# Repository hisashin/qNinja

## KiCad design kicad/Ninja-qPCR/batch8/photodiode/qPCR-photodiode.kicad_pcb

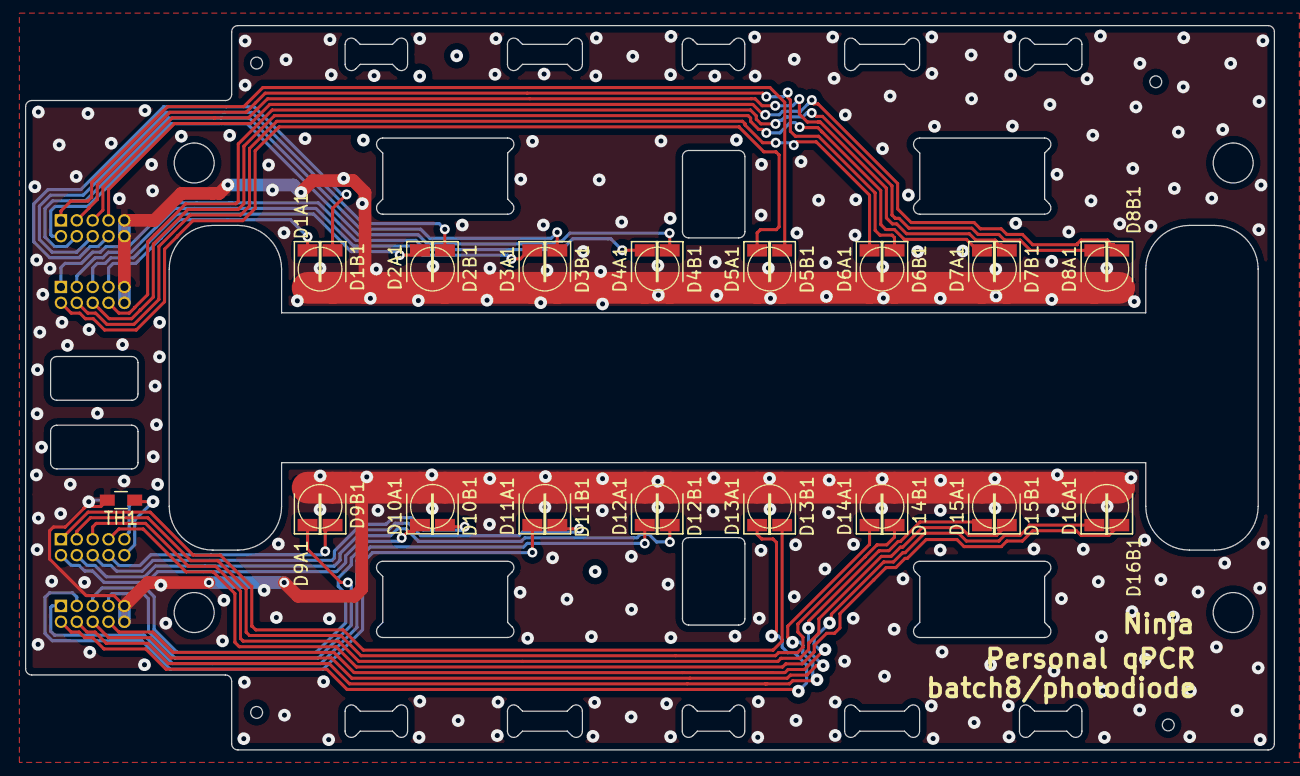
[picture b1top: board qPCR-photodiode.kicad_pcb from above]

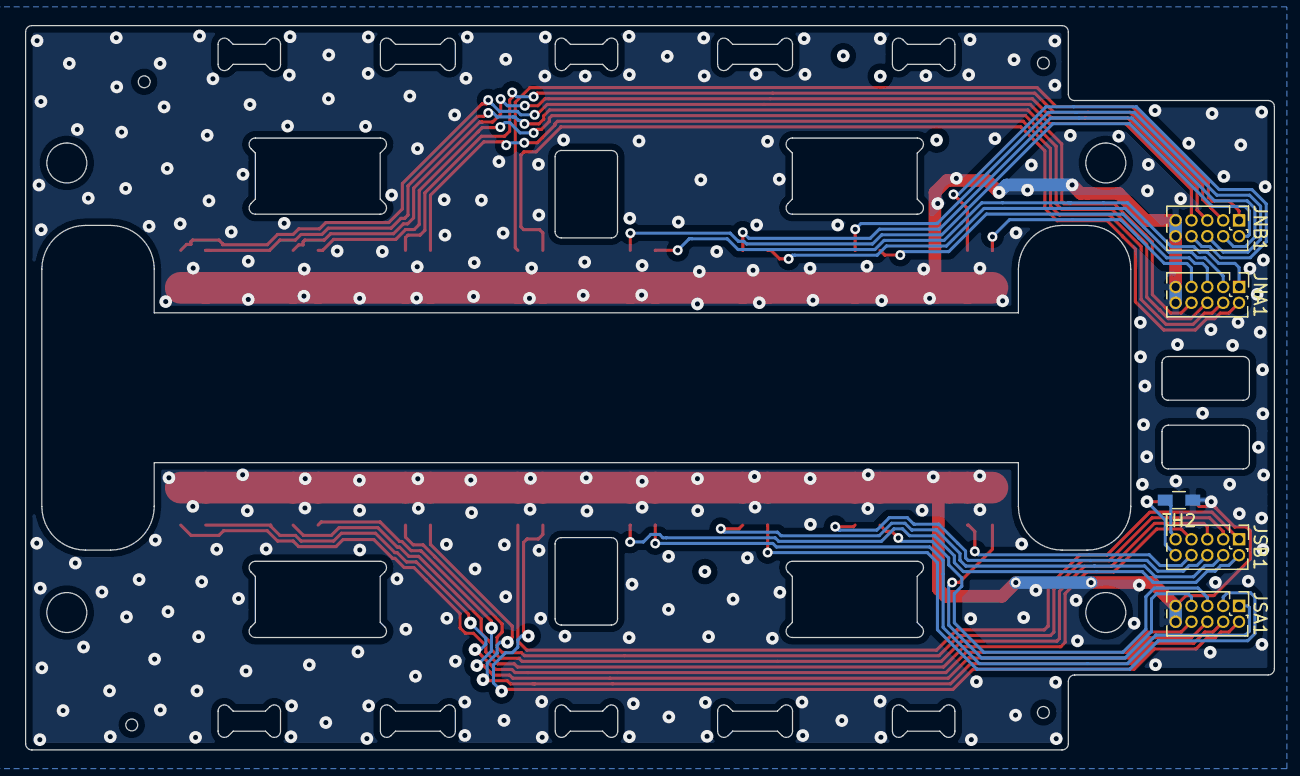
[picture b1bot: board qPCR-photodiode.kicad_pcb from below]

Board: 2 copper layers, 100.0 x 58.0 mm, 38 parts (5 on the bottom side), 35 nets.

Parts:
D1A1, D1B1, D2A1, D2B1, D3A1, D3B1, D4A1, D4B1, D5A1, D5B1, D6A1, D6B1, D7A1, D7B1, D8A1, D8B1, D9A1, D9B1, D10A1, D10B1, D11A1, D11B1, D12A1, D12B1, D13A1, D13B1, D14A1, D14B1, D15A1, D15B1, D16A1, D16B1: D_Photo; D_1206
JNA1: Conn_01x10_Male; Pin_Header_Straight_2x05_Pitch1.27mm
JNB1: Conn_01x10_Male; Pin_Header_Straight_2x05_Pitch1.27mm
JSA1: Conn_01x10_Male; Pin_Header_Straight_2x05_Pitch1.27mm
JSB1: Conn_01x10_Male; Pin_Header_Straight_2x05_Pitch1.27mm
TH1, TH2: Thermistor; R_0603_HandSoldering

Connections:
/N_PD_OUT1: D1A1.1, JNA1.7
/N_PD_OUT2: D1B1.1, JNB1.8
/N_PD_OUT3: D2A1.1, JNA1.5
/N_PD_OUT4: D2B1.1, JNB1.6
/N_PD_OUT5: D3A1.1, JNA1.3
/N_PD_OUT6: D3B1.1, JNB1.4
/N_PD_OUT7: D4A1.1, JNA1.1
/N_PD_OUT8: D4B1.1, JNB1.2
/N_PD_OUT9: D5A1.1, JNA1.2
/N_PD_OUT10: D5B1.1, JNB1.1
/N_PD_OUT11: D6A1.1, JNA1.4
/N_PD_OUT12: D6B1.1, JNB1.3
/N_PD_OUT13: D7A1.1, JNA1.6
/N_PD_OUT14: D7B1.1, JNB1.5
/N_PD_OUT15: D8A1.1, JNA1.8
/N_PD_OUT16: D8B1.1, JNB1.7
/S_PD_OUT1: D9A1.1, JSA1.7
/S_PD_OUT2: D9B1.1, JSB1.8
/S_PD_OUT3: D10A1.1, JSA1.5
/S_PD_OUT4: D10B1.1, JSB1.6
/S_PD_OUT5: D11A1.1, JSA1.3
/S_PD_OUT6: D11B1.1, JSB1.4
/S_PD_OUT7: D12A1.1, JSA1.1
/S_PD_OUT8: D12B1.1, JSB1.2
/S_PD_OUT9: D13A1.1, JSA1.2
/S_PD_OUT10: D13B1.1, JSB1.1
/S_PD_OUT11: D14A1.1, JSA1.4
/S_PD_OUT12: D14B1.1, JSB1.3
/S_PD_OUT13: D15A1.1, JSA1.6
/S_PD_OUT14: D15B1.1, JSB1.5
/S_PD_OUT15: D16A1.1, JSA1.8
/S_PD_OUT16: D16B1.1, JSB1.7
GNDA: D1A1.2, D1B1.2, D2A1.2, D2B1.2, D3A1.2, D3B1.2, D4A1.2, D4B1.2, D5A1.2, D5B1.2, D6A1.2, D6B1.2, D7A1.2, D7B1.2, D8A1.2, D8B1.2, D9A1.2, D9B1.2, D10A1.2, D10B1.2, D11A1.2, D11B1.2, D12A1.2, D12B1.2, D13A1.2, D13B1.2, D14A1.2, D14B1.2, D15A1.2, D15B1.2, D16A1.2, D16B1.2, JNA1.9, JNA1.10, JNB1.9, JNB1.10, JSA1.9, JSA1.10, TH1.2, TH2.2
unnamed: JSB1.9, TH2.1
unnamed: JSB1.10, TH1.1

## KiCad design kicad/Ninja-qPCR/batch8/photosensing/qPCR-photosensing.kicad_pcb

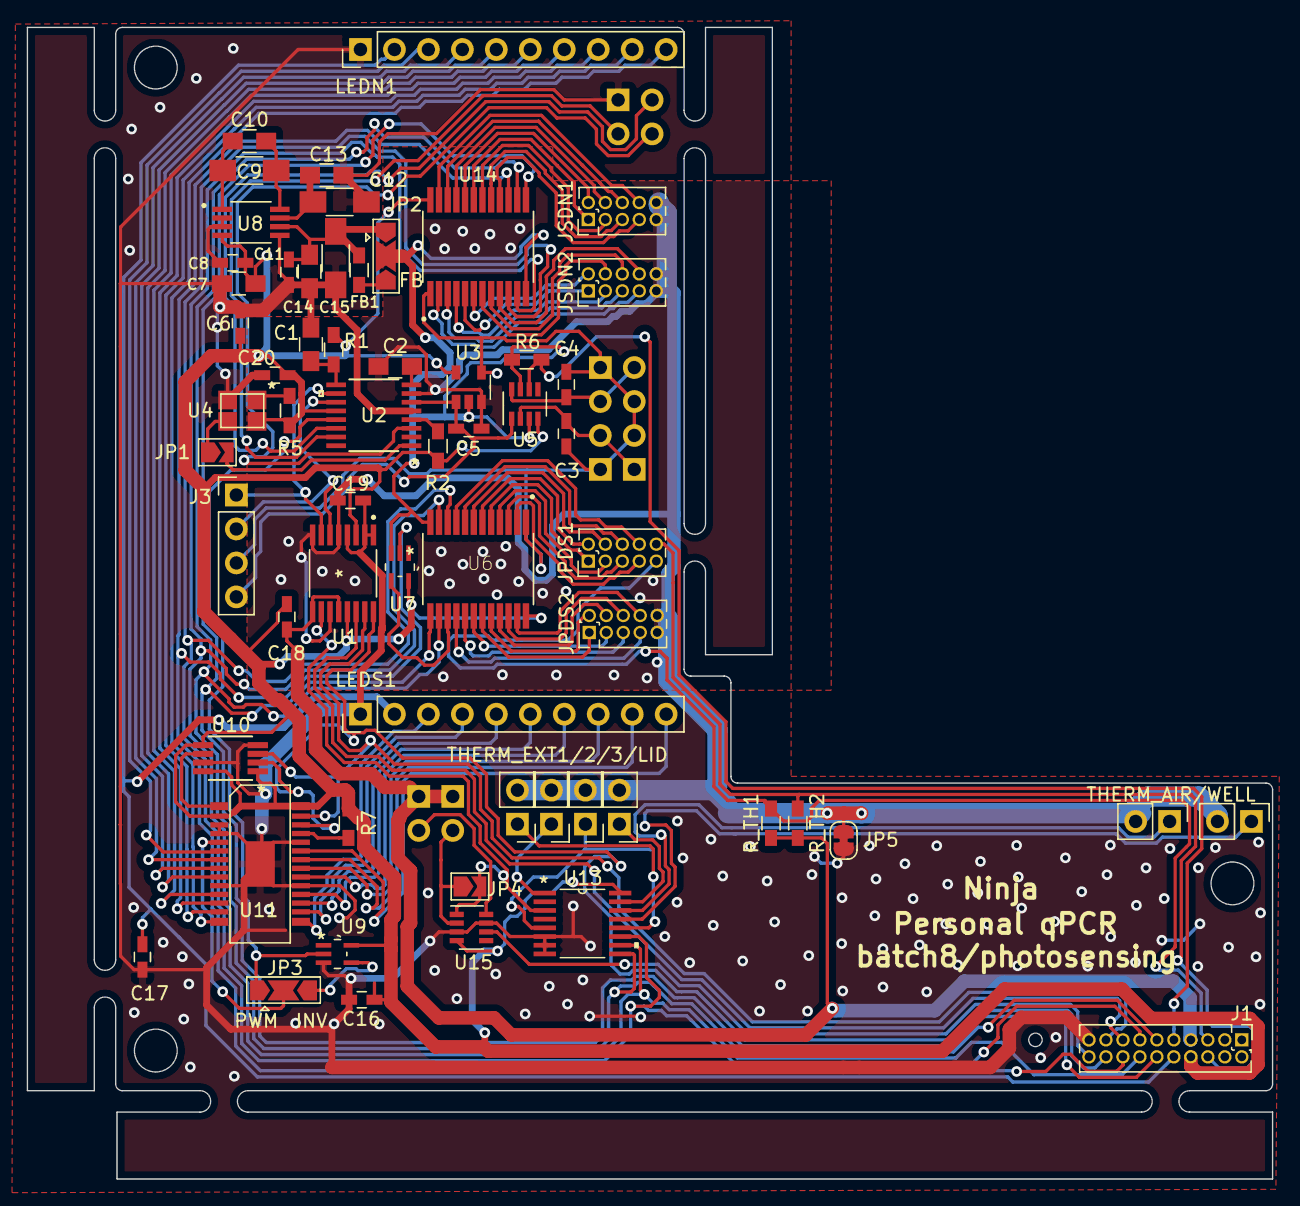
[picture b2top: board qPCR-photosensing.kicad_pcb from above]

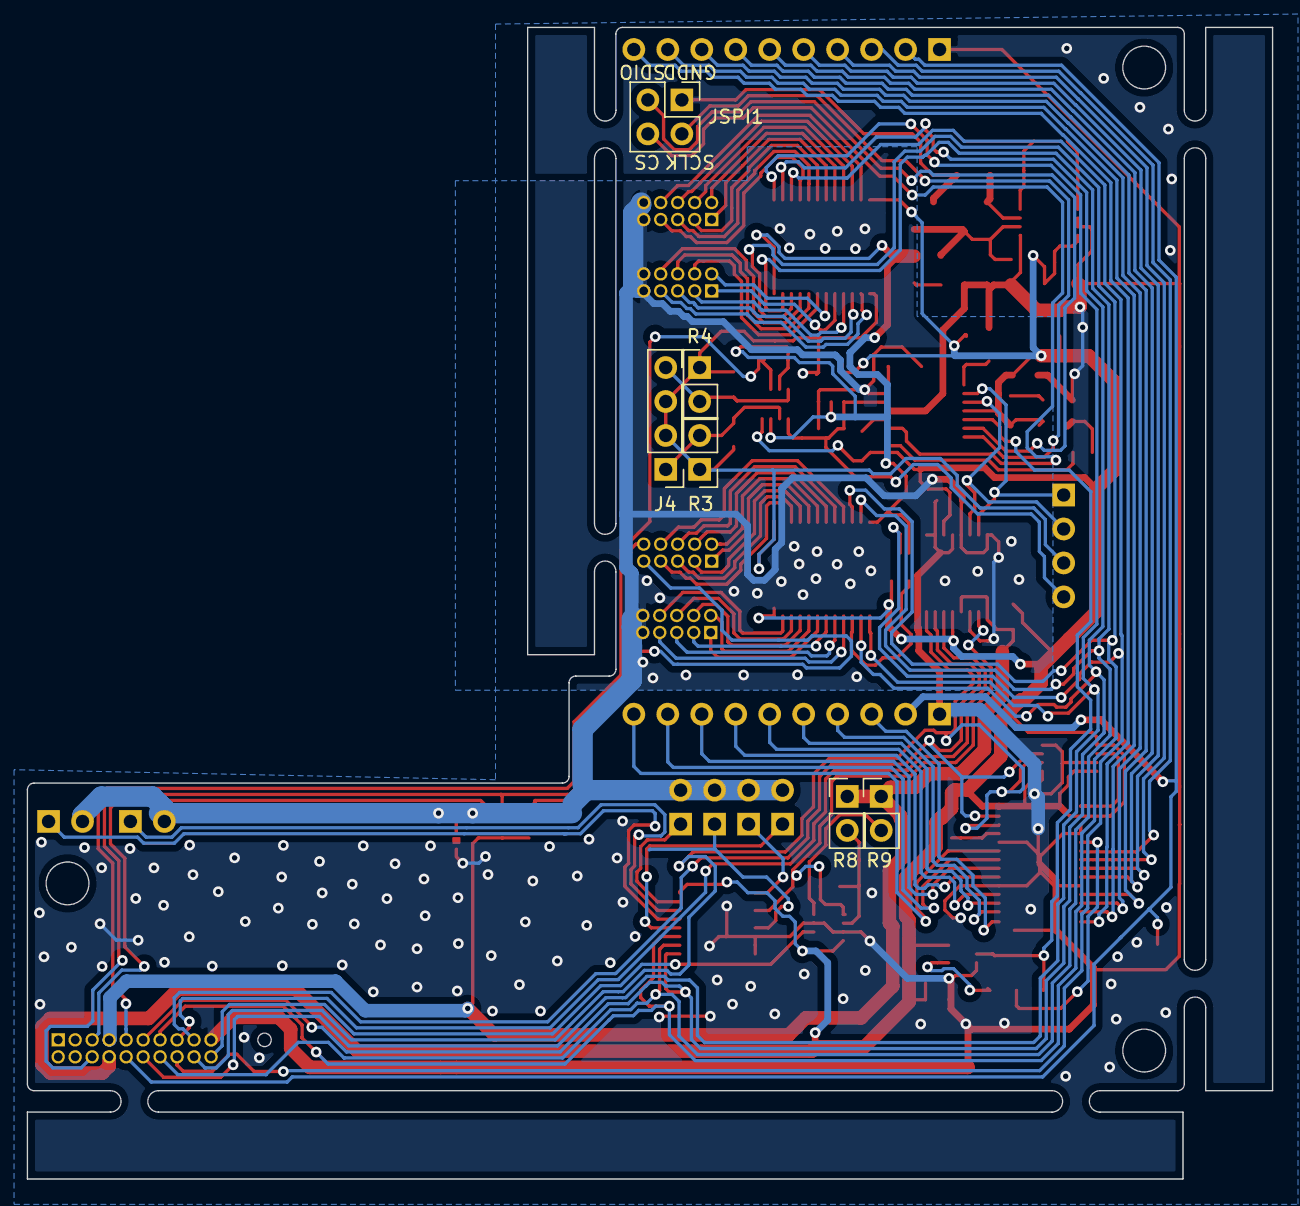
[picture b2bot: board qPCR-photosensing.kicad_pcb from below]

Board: 2 copper layers, 93.1 x 86.1 mm, 67 parts (6 on the bottom side), 101 nets.

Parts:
C1, C2, C7, C10, C13: 4.7uF; C_0805_HandSoldering
C3, C4: 22pF; C_0603_HandSoldering
C5, C6, C8, C11, C16, C17, C18, C19, C20: 0.1uF; C_0603_HandSoldering
C9, C12, C15: DNP; C_1206_HandSoldering
C14: 22uF; C_0805_HandSoldering
FB1: 120@100MHz; R_0603_HandSoldering
J1: Conn_01x20_Male; Pin_Header_Straight_2x10_Pitch1.27mm
J3, J4: Conn_01x04_Male; Pin_Header_Straight_1x04_Pitch2.54mm
JP1: Jumper; SolderJumper-2_P1.3mm_Open_TrianglePad1.0x1.5mm
JP2, JP3: Jumper_3_Open; SolderJumper-3_P2.0mm_Open_TrianglePad1.0x1.5mm
JP4: Jumper_2_Open; SolderJumper-2_P1.3mm_Open_TrianglePad1.0x1.5mm
JP5: SolderJumper_2_Bridged; SolderJumper-2_P1.3mm_Bridged_RoundedPad1.0x1.5mm
JPDS1, JPDS2: Conn_01x10_Male; Pin_Header_Straight_2x05_Pitch1.27mm
JSDN1, JSDN2: Conn_01x10_Male; Pin_Header_Straight_2x05_Pitch1.27mm
JSPI1: Conn_01x04_Male; Pin_Header_Straight_2x02_Pitch2.54mm
LEDN1: Conn_01x10_Male; Pin_Header_Straight_1x10_Pitch2.54mm
LEDS1: Conn_01x10_Male; Pin_Header_Straight_1x10_Pitch2.54mm
R1, R2, R5, R6: 10K; R_0603_HandSoldering
R3, R4: R; Pin_Header_Straight_1x02_Pitch2.54mm
R7: 47k; R_0603_HandSoldering
R8, R9: ?k; Pin_Header_Straight_1x02_Pitch2.54mm
R_TH1, R_TH2: 10K; R_0603_HandSoldering
TAIR1: Conn_01x02_Male; Pin_Header_Straight_1x02_Pitch2.54mm
TEXT1, TEXT2, TEXT3: Conn_01x02_Male; Pin_Header_Straight_1x02_Pitch2.54mm
TLID1: Conn_01x02_Male; Pin_Header_Straight_1x02_Pitch2.54mm
TWELL1: Conn_01x02_Male; Pin_Header_Straight_1x02_Pitch2.54mm
U1: ADS122C04IPWR
U2: ADA2200ARUZ
U3: LMP7717MF_NOPB; SOT-23-5
U4: COM1305-0.032768-EXT-T-TR
U5, U15: TS12A12511DCNR; SOT-23-8
U6, U14: CD74HC4067M96; SOP65P780X200-24N
U7, U9: SN74LVC1GU04DCKR
U8: LM7705MMX_NOPB; LM7705MMX-NOPB
U10: MCP4551T-503E/MS; MCP4551T-502E&slash_MS
U11: PCA9955B
U13: SN74LV4051APWR

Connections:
3V3A: C18.1, J1.7, R8.1, R9.1, R_TH1.2, R_TH2.2, U1.9, U1.12
3V3D: C6.1, C7.2, C8.2, C16.1, C18.2, C20.1, J1.8, R1.2, R2.2, R5.2, R7.2, U1.3, U1.13, U2.12, U3.5, U4.4, U5.4, U6.24, U7.5, U8.4, U9.5, U10.1, U10.5, U10.8, U11.2, U11.28, U13.16, U14.24, U15.4
-1V: JP2.2, R6.2, U3.2, U5.3, U5.7, U6.12, U7.3, U14.12
/AMP_OUT: C5.2, J3.4, U2.6, U3.1, U5.1
/GAIN_LARGE: C3.1, J4.1, R3.2, U5.2
/GAIN_SMALL: C4.1, J4.4, R4.2, U5.8
/LED/LED_BLANK: JP3.2, U11.5
/LED/LED_IREF: U10.6, U11.1
/PHOTO_OUT_N: J3.1, U1.7, U2.10
/PHOTO_OUT_P: J3.2, U1.6, U2.11
/Sheet60AF0517/MUX_SELECT_INV: U6.15, U7.4
/Sheet60AF0517/S_PD_OUT1: JPDS2.8, U6.23
/Sheet60AF0517/S_PD_OUT2: JPDS1.7, U6.2
/Sheet60AF0517/S_PD_OUT3: JPDS2.6, U6.22
/Sheet60AF0517/S_PD_OUT4: JPDS1.5, U6.3
/Sheet60AF0517/S_PD_OUT5: JPDS2.4, U6.21
/Sheet60AF0517/S_PD_OUT6: JPDS1.3, U6.4
/Sheet60AF0517/S_PD_OUT7: JPDS2.2, U6.20
/Sheet60AF0517/S_PD_OUT8: JPDS1.1, U6.5
/Sheet60AF0517/S_PD_OUT9: JPDS2.1, U6.19
/Sheet60AF0517/S_PD_OUT10: JPDS1.2, U6.6
/Sheet60AF0517/S_PD_OUT11: JPDS2.3, U6.18
/Sheet60AF0517/S_PD_OUT12: JPDS1.4, U6.7
/Sheet60AF0517/S_PD_OUT13: JPDS2.5, U6.17
/Sheet60AF0517/S_PD_OUT14: JPDS1.6, U6.8
/Sheet60AF0517/S_PD_OUT15: JPDS2.7, U6.16
/Sheet60AF0517/S_PD_OUT16: JPDS1.8, U6.9
/Sheet60C04E5B/N_PD_OUT1: JSDN2.8, U14.9
/Sheet60C04E5B/N_PD_OUT2: JSDN1.7, U14.16
/Sheet60C04E5B/N_PD_OUT3: JSDN2.6, U14.8
/Sheet60C04E5B/N_PD_OUT4: JSDN1.5, U14.17
/Sheet60C04E5B/N_PD_OUT5: JSDN2.4, U14.7
/Sheet60C04E5B/N_PD_OUT6: JSDN1.3, U14.18
/Sheet60C04E5B/N_PD_OUT7: JSDN2.2, U14.6
/Sheet60C04E5B/N_PD_OUT8: JSDN1.1, U14.19
/Sheet60C04E5B/N_PD_OUT9: JSDN2.1, U14.5
/Sheet60C04E5B/N_PD_OUT10: JSDN1.2, U14.20
/Sheet60C04E5B/N_PD_OUT11: JSDN2.3, U14.4
/Sheet60C04E5B/N_PD_OUT12: JSDN1.4, U14.21
/Sheet60C04E5B/N_PD_OUT13: JSDN2.5, U14.3
/Sheet60C04E5B/N_PD_OUT14: JSDN1.6, U14.22
/Sheet60C04E5B/N_PD_OUT15: JSDN2.7, U14.2
/Sheet60C04E5B/N_PD_OUT16: JSDN1.8, U14.23
ADC_DRDY: J1.15, U1.14
AMP_GAIN_SW: J1.9, R6.1, U5.6
CLKIN: JP1.2, U2.1
DEMOD_SPI_CS: JSPI1.4, U2.3
DEMOD_SPI_SCLK: JSPI1.2, U2.15
DEMOD_SPI_SDIO: JSPI1.3, U2.14
GNDA: C2.2, C5.1, C19.1, JP5.2, JPDS2.9, JPDS2.10, JSDN1.9, JSDN1.10, JSDN2.9, JSDN2.10, TAIR1.2, TEXT1.2, TEXT2.2, TEXT3.2, TLID1.2, TWELL1.2, U1.5, U1.8, U1.11, U2.7, U3.3
GNDD: C1.2, C6.2, C7.1, C8.1, C11.1, C12.1, C13.1, C14.1, C15.1, C16.2, C17.2, C19.2, C20.2, J1.19, JP5.1, JSPI1.1, LEDN1.1, LEDS1.1, U1.1, U1.2, U1.4, U2.5, U4.2, U8.2, U8.3, U8.5, U9.3, U10.4, U10.7, U11.3, U11.4, U11.10, U11.19, U11.24, U11.29, U13.6, U13.7, U13.8, U15.3, U15.7
I2C_SCL: J1.18, U1.16, U10.2, U11.26
I2C_SDA: J1.17, U1.15, U10.3, U11.27
MUX_S0: J1.13, U6.10, U13.11, U14.10
MUX_S1: J1.14, U6.11, U13.10, U14.11
MUX_S2: J1.11, U6.14, U13.9, U14.14
MUX_S3: J1.12, U6.13, U14.13
MUX_SELECT: J1.16, U7.2, U14.15
N_LED_OUT1: LEDN1.3, U11.6
N_LED_OUT2: LEDN1.4, U11.7
N_LED_OUT3: LEDN1.5, U11.8
N_LED_OUT4: LEDN1.6, U11.9
N_LED_OUT5: LEDN1.7, U11.11
N_LED_OUT6: LEDN1.8, U11.12
N_LED_OUT7: LEDN1.9, U11.13
N_LED_OUT8: LEDN1.10, U11.14
unnamed: C1.1, R1.1, U2.9
unnamed: C2.1, U2.8
unnamed: C9.1, C10.1, U8.8
unnamed: C9.2, C10.2, U8.1
unnamed: C11.2, C14.2, C15.2, FB1.2, JP2.1, U8.6
unnamed: C12.2, C13.2, U8.7
unnamed: FB1.1, JP2.3
unnamed: JP1.1, U4.3
unnamed: JP3.3, U9.4
unnamed: JP4.1, R8.2, U15.2
unnamed: R2.1, U2.4
unnamed: R5.1, U4.1
unnamed: R7.1, U11.25
unnamed: R9.2, U15.8
PD_MUX_OUT: C3.2, C4.2, J3.3, J4.2, J4.3, R3.1, R4.1, U3.4, U6.1, U14.1
PD_REF_PWM: JP3.1, U2.13, U9.2
PD_TH1: J1.5, JPDS1.9, R_TH1.1
PD_TH2: J1.6, JPDS1.10, R_TH2.1
S_LED_OUT1: LEDS1.3, U11.15
S_LED_OUT2: LEDS1.4, U11.16
S_LED_OUT3: LEDS1.5, U11.17
S_LED_OUT4: LEDS1.6, U11.18
S_LED_OUT5: LEDS1.7, U11.20
S_LED_OUT6: LEDS1.8, U11.21
S_LED_OUT7: LEDS1.9, U11.22
S_LED_OUT8: LEDS1.10, U11.23
THERM_AIR: TAIR1.1, U13.14
THERM_EXT1: TEXT1.1, U13.12
THERM_EXT2: TEXT2.1, U13.1
THERM_EXT3: TEXT3.1, U13.5
THERM_LID: TLID1.1, U13.15
THERM_MUX_OUT: JP4.2, U1.10, U13.3, U15.1
THERM_R_SWITCH: J1.20, U15.6
THERM_WELL: TWELL1.1, U13.13
VCC_LED: C17.1, J1.10, LEDN1.2, LEDS1.2

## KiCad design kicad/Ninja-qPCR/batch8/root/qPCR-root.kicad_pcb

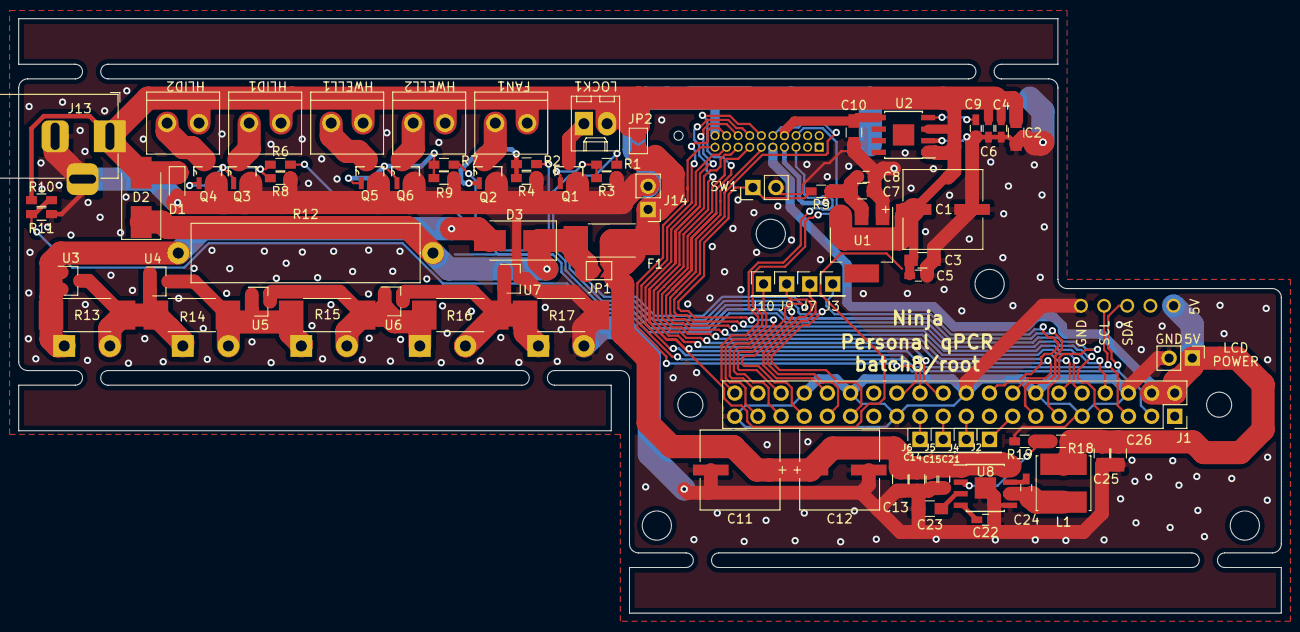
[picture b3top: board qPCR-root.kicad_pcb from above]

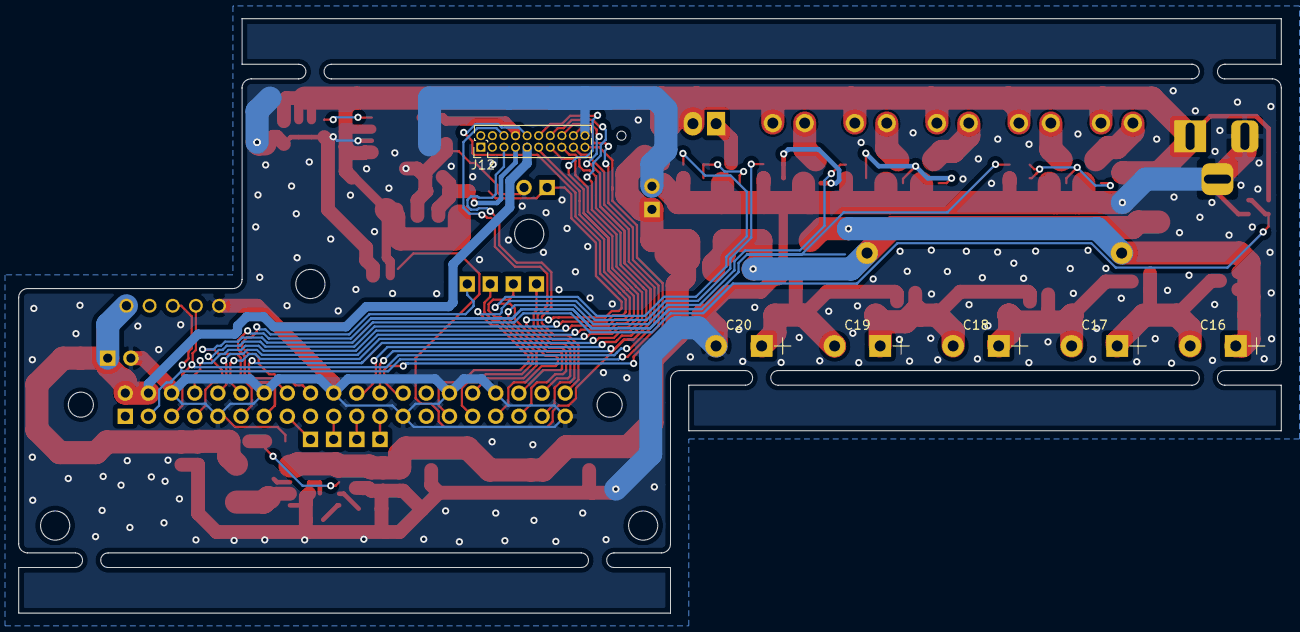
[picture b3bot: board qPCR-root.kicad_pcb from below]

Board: 2 copper layers, 138.5 x 65.2 mm, 87 parts (6 on the bottom side), 54 nets.

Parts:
C1, C11, C12: 100uF; UWX1E101MCL1GB
C2, C10, C13, C14, C23: 4.7uF; C_0805_HandSoldering
C3, C7, C25, C26: 22uF; C_0805_HandSoldering
C4, C5, C8, C15, C24: 0.1uF; C_0603_HandSoldering
C6, C21, C22: 0.01uF; C_0603_HandSoldering
C9: 100pF; C_0603_HandSoldering
C16, C17, C18, C19, C20: 10F2.7V; CP_Radial_P5.00mm
D1: D_Schottky; D_SOD-323_HandSoldering
D2, D3: D; D_SMB_Handsoldering
F1: Fuse; R_2512_HandSoldering
FAN1: Screw_Terminal_01x02; TB_SeeedOPL_320110028
HLID1, HLID2: Screw_Terminal_01x02; TB_SeeedOPL_320110028
HWELL1, HWELL2: Screw_Terminal_01x02; TB_SeeedOPL_320110028
J1: Raspberry_Pi_3A_Plus_wpi; Raspberry_Pi_3A+_3B+_4B_FaceDown_TopOnly
J2, J3, J4, J5, J6, J7, J9, J10: Conn_01x01_Male; Pin_Header_Straight_1x01_Pitch2.54mm
J12: Conn_01x20_Male; Pin_Header_Straight_2x10_Pitch1.27mm
J13: Barrel_Jack_Switch; BarrelJack_Horizontal
J14: Conn_01x02_Male; Pin_Header_Straight_1x02_Pitch2.54mm
JP1, JP2: Jumper; SolderJumper-2_P1.3mm_Open_TrianglePad1.0x1.5mm
L1: 3.3uH(ALPS GLMC / TDK SPM6530); SRN6045TA-3R3Y
LCD1: RPI_LCD_TOUCH_7INCH; RPI_LCD_TOUCH_7INCH_M2.5NONE
LCD1_POWER1: Conn_01x02_Male; Pin_Header_Straight_1x02_Pitch2.54mm
LOCK1: Conn_01x02_Male; Molex_KK-6410-02_02x2.54mm_Straight
Q1, Q2, Q3, Q4, Q5, Q6: Q_NMOS_GSD; SOT95P240X112-3N
R1, R2, R6, R7: 150; R_0603_HandSoldering
R3, R4, R5, R8, R9, R10, R19: 47k; R_0603_HandSoldering
R11: 10k; R_0603_HandSoldering
R12: 8.2Ω 3W; R_Axial_Power_L25.0mm_W6.4mm_P27.94mm
R13, R14, R15, R16, R17: 1k2W; R_2512_HandSoldering
R18: 261k; R_0603_HandSoldering
SW1: SW_Reed; Pin_Header_Straight_1x02_Pitch2.54mm
U1: CJT1117-3.3; SOT-223
U2: AP2210K-3.3TRG1; SOIC-8-1EP_3.9x4.9mm_Pitch1.27mm
U3, U4, U5, U6, U7: TL431DBZ; SOT-23
U8: BD9D320EFJ-E2; SOIC-8-1EP_3.9x4.9mm_Pitch1.27mm

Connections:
3V3A: C10.1, J12.8, U2.5
3V3D: C7.1, C8.1, J12.7, R5.1, U1.2
5V_UPS: C25.1, C26.1, J1.2, J1.4, J12.9, L1.2, LCD1.1, LCD1_POWER1.1, R18.1
12V: C1.1, C2.1, C3.1, C4.1, C5.1, C6.1, D1.1, D2.2, FAN1.1, HLID1.1, HLID2.1, HWELL1.1, HWELL2.1, J13.1, JP2.1, LOCK1.2, R10.1, U1.3, U2.1, U2.3
12V_BD_VIN: C11.1, C12.1, C13.1, C14.1, C15.1, C21.1, F1.1, J14.1, JP1.2, JP2.2, U8.1, U8.8
/FAN: J1.29, R2.2
/GPIO3: J1.15, J2.1
/GPIO5: J1.18, J3.1
/GPIO12: J1.19, J4.1
/GPIO13: J1.21, J5.1
/GPIO14: J1.23, J6.1
/GPIO22: J1.31, J7.1
/GPIO26: J1.32, J9.1
/GPIO28: J1.38, J10.1
/LID_HEATER: J1.13, R6.2
/SheetSupercap/BD_BOOT: C24.1, U8.7
/SheetSupercap/BD_FB: R18.2, R19.1, U8.2
/SheetSupercap/BD_SW: C24.2, L1.1, U8.6
/WELL_HEATER: J1.33, R7.2
ADC_DRDY: J1.24, J12.16
AMP_GAIN_SW: J1.7, J12.10
DLOCK: J1.36, R1.2
DOPEN: J1.35, R5.2, SW1.1
GND: C1.2, C2.2, C3.2, C4.2, C5.2, C6.2, C7.2, C8.2, C9.2, C10.2, C11.2, C12.2, C13.2, C14.2, C15.2, C20.2, C21.2, C22.2, C23.2, C25.2, C26.2, D1.2, J1.6, J1.9, J1.14, J1.20, J1.25, J1.30, J1.34, J1.39, J12.20, J13.2, J13.3, J14.2, LCD1.5, LCD1_POWER1.2, Q1.2, Q2.2, Q3.2, Q4.2, Q5.2, Q6.2, R3.1, R4.1, R8.1, R9.1, R11.2, R17.1, R19.2, SW1.2, U1.1, U2.2, U7.3, U8.5, U8.9
I2C_SCL: J1.5, J12.17, LCD1.4
I2C_SDA: J1.3, J12.18, LCD1.3
MUX_S0: J1.16, J12.14
MUX_S1: J1.12, J12.13
MUX_S2: J1.10, J12.12
MUX_S3: J1.8, J12.11
MUX_SELECT: J1.22, J12.15
unnamed: C9.1, U2.4
unnamed: C16.1, D3.2, R12.1, R13.2, U3.1, U3.2
unnamed: C16.2, C17.1, R13.1, R14.2, U3.3, U4.1, U4.2
unnamed: C17.2, C18.1, R14.1, R15.2, U4.3, U5.1, U5.2
unnamed: C18.2, C19.1, R15.1, R16.2, U5.3, U6.1, U6.2
unnamed: C19.2, C20.1, R16.1, R17.2, U6.3, U7.1, U7.2
unnamed: C22.1, U8.4
unnamed: C23.1, U8.3
unnamed: D2.1, D3.1, F1.2, JP1.1, R12.2
unnamed: FAN1.2, Q2.3
unnamed: HLID1.2, Q3.3
unnamed: HLID2.2, Q4.3
unnamed: HWELL1.2, Q5.3
unnamed: HWELL2.2, Q6.3
unnamed: LOCK1.1, Q1.3
unnamed: Q1.1, R1.1, R3.2
unnamed: Q2.1, R2.1, R4.2
unnamed: Q3.1, Q4.1, R6.1, R8.2
unnamed: Q5.1, Q6.1, R7.1, R9.2
PD_TH1: J1.37, J12.6
PD_TH2: J1.40, J12.5
THERM_R_SWITCH: J1.26, J12.19
VIN_SENSE: J1.11, R10.2, R11.1

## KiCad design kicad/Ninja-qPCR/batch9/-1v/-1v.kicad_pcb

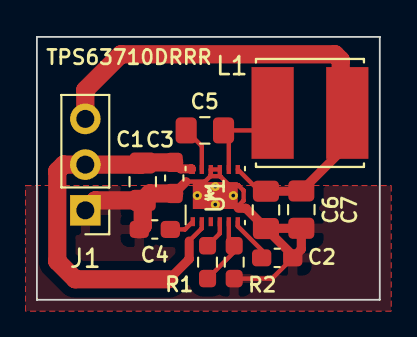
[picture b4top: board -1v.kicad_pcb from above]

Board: 2 copper layers, 19.1 x 14.6 mm, 12 parts (0 on the bottom side), 9 nets.

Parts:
C1, C6, C7: 22uF; C_0805_2012Metric_Pad1.18x1.45mm_HandSolder
C2: 1uF; C_0603_1608Metric_Pad1.08x0.95mm_HandSolder
C3: 2.2uF; C_0603_1608Metric_Pad1.08x0.95mm_HandSolder
C4: 220nF; C_0603_1608Metric_Pad1.08x0.95mm_HandSolder
C5: 10uF; C_0805_2012Metric_Pad1.18x1.45mm_HandSolder
J1: Conn_01x03_Female; Pin_Header_Straight_1x03_Pitch2.54mm
L1: 22uH; SRN6045TA-3R3Y
R1: 51.1k; R_0603_1608Metric_Pad0.98x0.95mm_HandSolder
R2: 180k; R_0603_1608Metric_Pad0.98x0.95mm_HandSolder
U1: TPS63710DRRR

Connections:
3V3: C1.1, C3.1, J1.2, U1.2, U1.12
-1V: C6.1, C7.1, J1.3, L1.2, U1.7
GND: C1.2, C2.2, C3.2, C4.2, C6.2, C7.2, J1.1, R2.2, U1.9, U1.10, U1.13
unnamed: C2.1, U1.6
unnamed: C4.1, U1.1
unnamed: C5.1, U1.11
unnamed: C5.2, L1.1, U1.8
unnamed: R1.1, U1.4
unnamed: R1.2, R2.1, U1.5

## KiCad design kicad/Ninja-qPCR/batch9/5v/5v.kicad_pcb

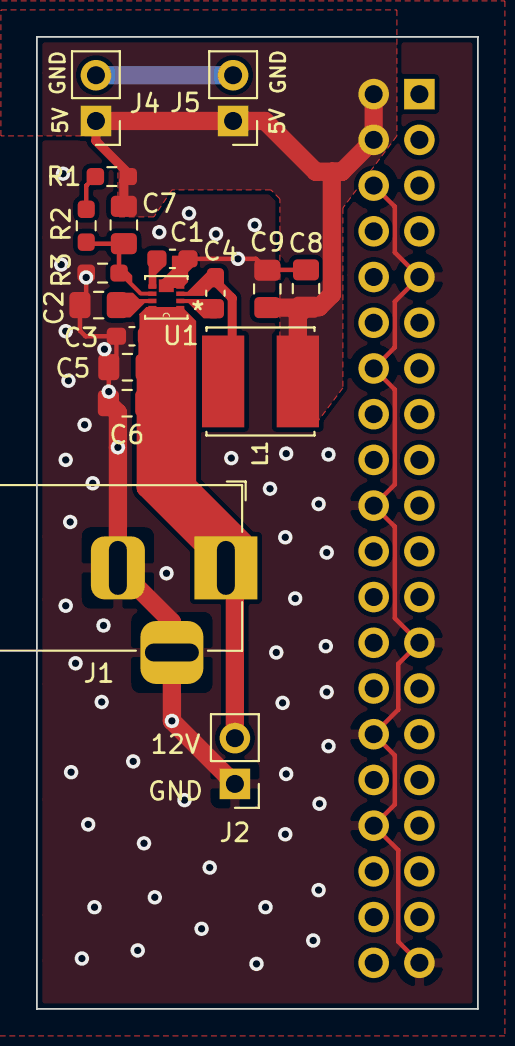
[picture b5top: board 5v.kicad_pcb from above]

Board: 2 copper layers, 24.5 x 54.0 mm, 19 parts (1 on the bottom side), 9 nets.

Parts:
C1: 330pF; C_0603_1608Metric_Pad1.08x0.95mm_HandSolder
C2: 1uF; C_0805_2012Metric_Pad1.18x1.45mm_HandSolder
C3, C4: 0.1uF; C_0603_1608Metric_Pad1.08x0.95mm_HandSolder
C5, C6: 10uF; C_0805_2012Metric_Pad1.18x1.45mm_HandSolder
C7: 22pF; C_0805_2012Metric_Pad1.18x1.45mm_HandSolder
C8, C9: 22uF; C_0805_2012Metric_Pad1.18x1.45mm_HandSolder
J1: Barrel_Jack_Switch; BarrelJack_Horizontal
J2, J4, J5: Conn_01x02_Female; Pin_Header_Straight_1x02_Pitch2.54mm
J8: Conn_02x20_Odd_Even; Pin_Header_Straight_2x20_Pitch2.54mm
L1: 3.3uF; SRN6045TA-3R3Y
R1: 1.8k; R_0603_1608Metric_Pad0.98x0.95mm_HandSolder
R2: 120k; R_0603_1608Metric_Pad0.98x0.95mm_HandSolder
R3: 22k; R_0603_1608Metric_Pad0.98x0.95mm_HandSolder
U1: UMMP008Z2020_ROM; BD9D323QWZ-E2

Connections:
5V: C7.2, C8.2, C9.2, J4.1, J5.1, J8.2, J8.4, L1.1, R1.1
12V: C3.2, C5.2, C6.2, J1.1, J2.2, U1.1, U1.8
/FB: C7.1, R2.2, R3.1, U1.6
/SS: C1.2, U1.5
GND: C1.1, C2.1, C3.1, C5.1, C6.1, C8.1, C9.1, J1.2, J1.3, J2.1, J4.2, J5.2, J8.6, J8.9, J8.14, J8.20, J8.25, J8.30, J8.34, J8.39, R3.2, U1.4, U1.9
unnamed: C2.2, U1.7
unnamed: C4.1, L1.2, U1.3
unnamed: C4.2, U1.2
unnamed: R1.2, R2.1

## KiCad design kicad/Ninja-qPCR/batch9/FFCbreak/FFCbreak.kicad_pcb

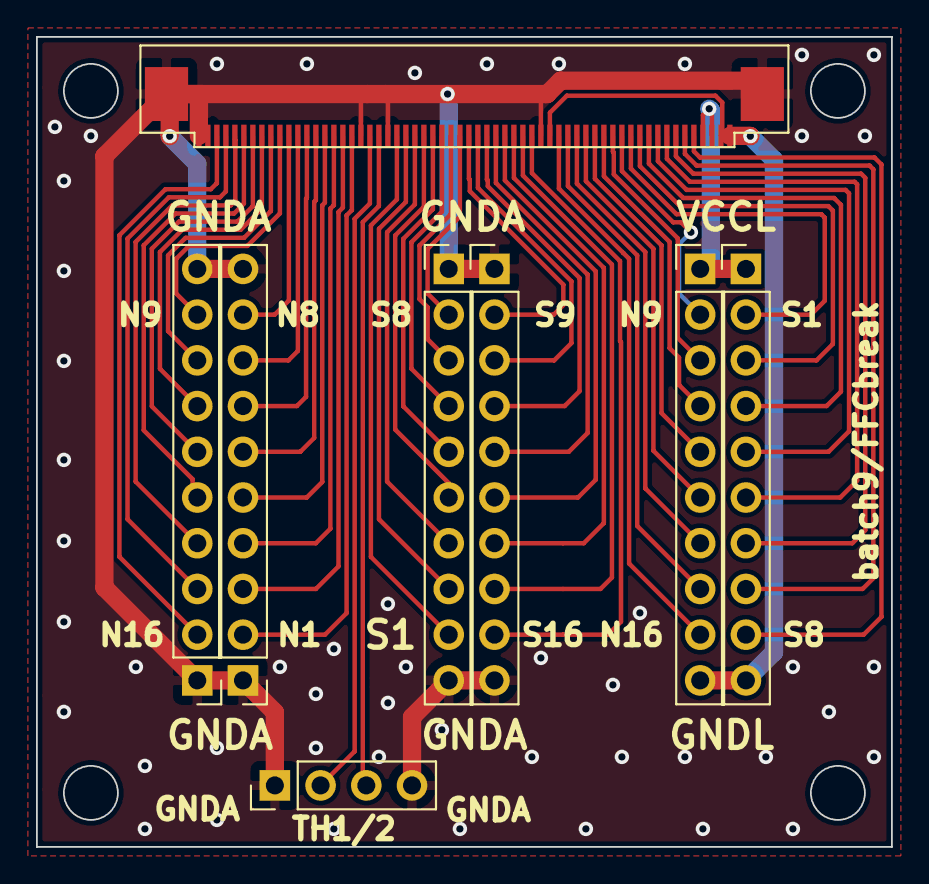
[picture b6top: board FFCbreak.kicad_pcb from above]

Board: 2 copper layers, 47.5 x 45.0 mm, 8 parts (0 on the bottom side), 53 nets.

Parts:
J1: Conn_01x60_Male; FFC_60_Ali_HUISHUNFA
J2, J3, J4, J5, J6, J7: Conn_01x10_Male; Pin_Header_Straight_1x10_Pitch2.54mm
J8: Conn_01x04_Male; Pin_Header_Straight_1x04_Pitch2.54mm

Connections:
/N_LED_OUT9: J1.13, J3.2
/N_LED_OUT10: J1.14, J3.3
/N_LED_OUT11: J1.15, J3.4
/N_LED_OUT12: J1.16, J3.5
/N_LED_OUT13: J1.17, J3.6
/N_LED_OUT14: J1.18, J3.7
/N_LED_OUT15: J1.19, J3.8
/N_LED_OUT16: J1.20, J3.9
/N_PD_OUT1: J1.43, J6.2
/N_PD_OUT2: J1.44, J6.3
/N_PD_OUT3: J1.45, J6.4
/N_PD_OUT4: J1.46, J6.5
/N_PD_OUT5: J1.47, J6.6
/N_PD_OUT6: J1.48, J6.7
/N_PD_OUT7: J1.49, J6.8
/N_PD_OUT8: J1.50, J6.9
/N_PD_OUT9: J1.51, J7.9
/N_PD_OUT10: J1.52, J7.8
/N_PD_OUT11: J1.53, J7.7
/N_PD_OUT12: J1.54, J7.6
/N_PD_OUT13: J1.55, J7.5
/N_PD_OUT14: J1.56, J7.4
/N_PD_OUT15: J1.57, J7.3
/N_PD_OUT16: J1.58, J7.2
/S_LED_OUT1: J1.12, J2.2
/S_LED_OUT2: J1.11, J2.3
/S_LED_OUT3: J1.10, J2.4
/S_LED_OUT4: J1.9, J2.5
/S_LED_OUT5: J1.8, J2.6
/S_LED_OUT6: J1.7, J2.7
/S_LED_OUT7: J1.6, J2.8
/S_LED_OUT8: J1.5, J2.9
/S_PD_OUT1: J1.38, J4.9
/S_PD_OUT2: J1.37, J4.8
/S_PD_OUT3: J1.36, J4.7
/S_PD_OUT4: J1.35, J4.6
/S_PD_OUT5: J1.34, J4.5
/S_PD_OUT6: J1.33, J4.4
/S_PD_OUT7: J1.32, J4.3
/S_PD_OUT8: J1.31, J4.2
/S_PD_OUT9: J1.30, J5.2
/S_PD_OUT10: J1.29, J5.3
/S_PD_OUT11: J1.28, J5.4
/S_PD_OUT12: J1.27, J5.5
/S_PD_OUT13: J1.26, J5.6
/S_PD_OUT14: J1.25, J5.7
/S_PD_OUT15: J1.24, J5.8
/S_PD_OUT16: J1.23, J5.9
/TH1: J1.41, J8.2
/TH2: J1.40, J8.3
GNDA: J1.22, J1.39, J1.42, J1.59, J1.60, J1.G1, J1.G2, J4.1, J4.10, J5.1, J5.10, J6.1, J6.10, J7.1, J7.10, J8.1, J8.4
GNDL: J1.1, J1.2, J1.21, J2.10, J3.10
VCCL: J1.3, J1.4, J2.1, J3.1

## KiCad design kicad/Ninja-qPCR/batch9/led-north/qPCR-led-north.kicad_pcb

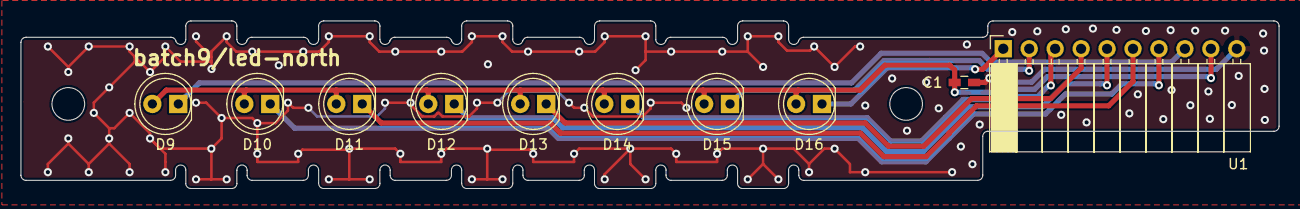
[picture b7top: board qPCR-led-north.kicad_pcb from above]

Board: 2 copper layers, 123.1 x 16.4 mm, 10 parts (0 on the bottom side), 10 nets.

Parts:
C1: C; C_0603_HandSoldering
D9, D10, D11, D12, D13, D14, D15, D16: LED; LED_D5.0mm
U1: Conn_02x05; Socket_Strip_Angled_1x10_Pitch2.54mm

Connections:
GND: C1.2, U1.10
OUT9: D9.1, U1.8
OUT10: D10.1, U1.7
OUT11: D11.1, U1.6
OUT12: D12.1, U1.5
OUT13: D13.1, U1.4
OUT14: D14.1, U1.3
OUT15: D15.1, U1.2
OUT16: D16.1, U1.1
VCC: C1.1, D9.2, D10.2, D11.2, D12.2, D13.2, D14.2, D15.2, D16.2, U1.9

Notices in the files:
parts and their libraries:
Copyright 2021 Accelerated Designs. All rights reserved.
Copyright 2016 Accelerated Designs. All rights reserved.
